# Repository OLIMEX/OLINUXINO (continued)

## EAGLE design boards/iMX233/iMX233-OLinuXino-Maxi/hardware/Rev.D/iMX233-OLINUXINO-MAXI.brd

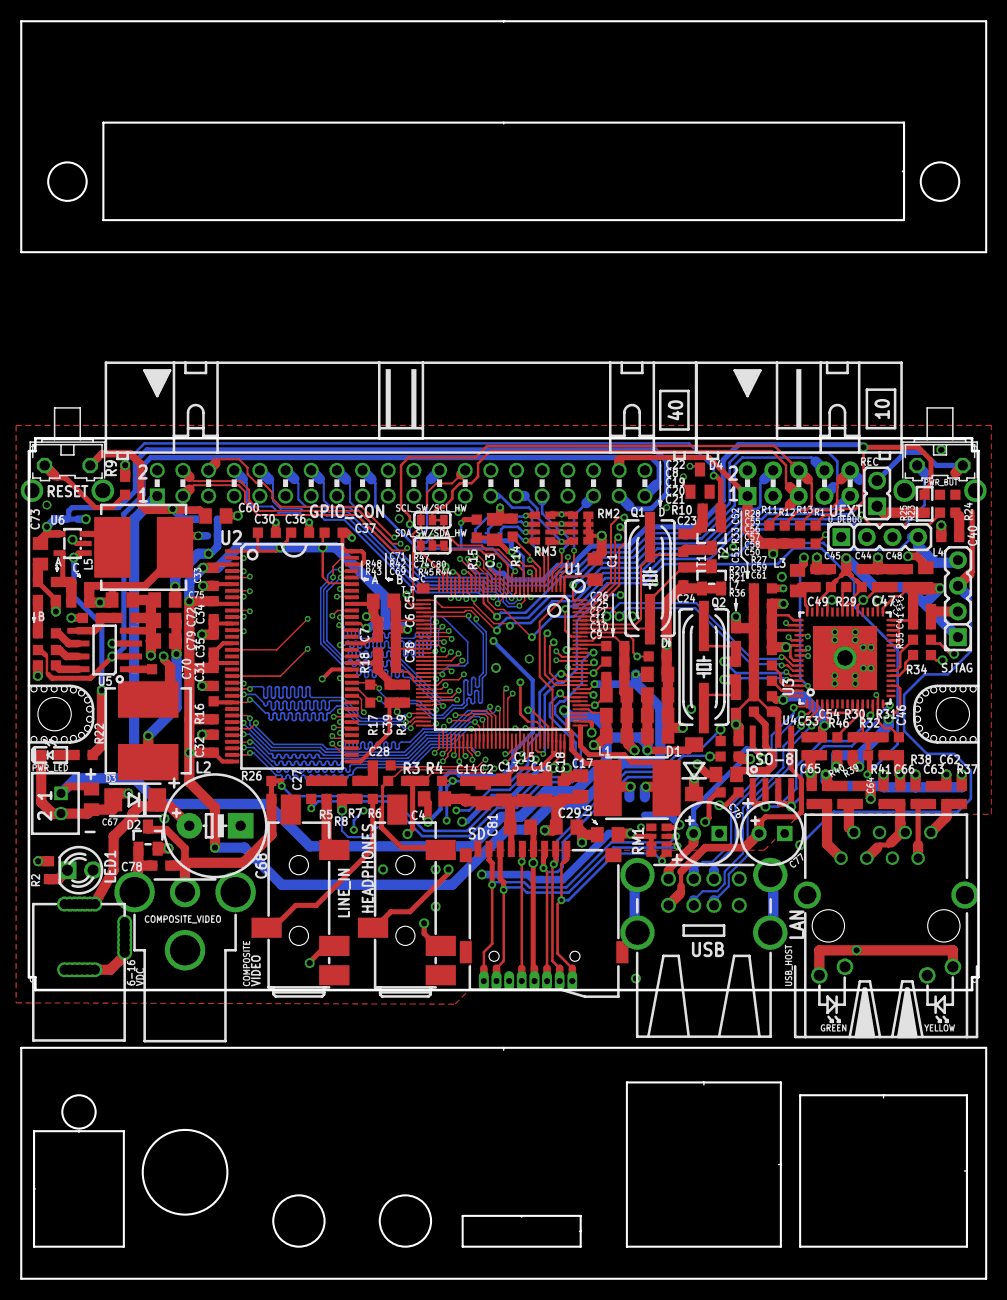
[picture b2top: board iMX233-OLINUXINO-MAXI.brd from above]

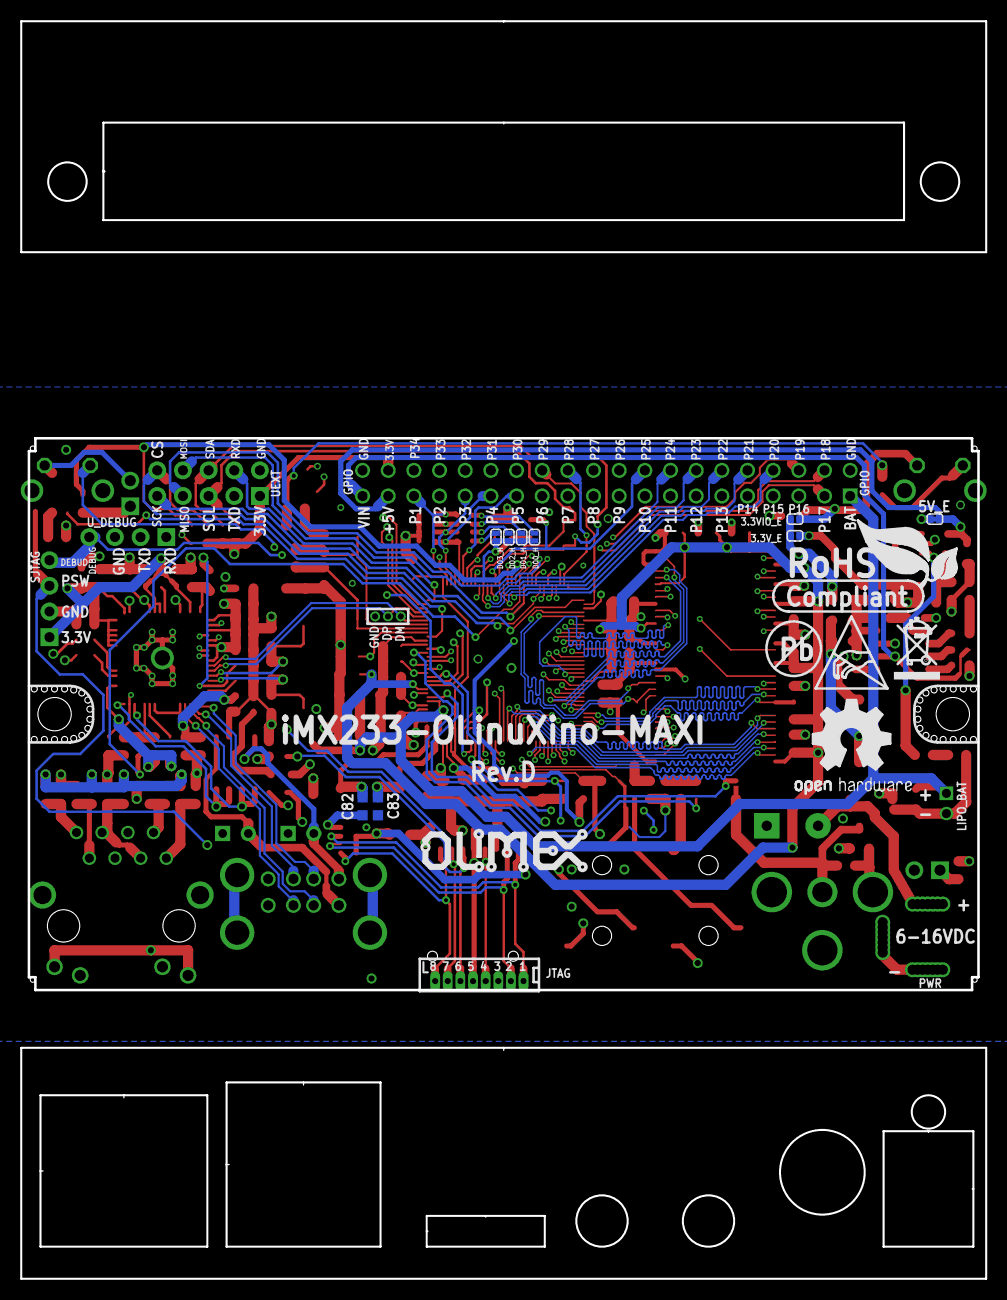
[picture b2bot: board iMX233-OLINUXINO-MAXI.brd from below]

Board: 4 copper layers, 94.0 x 54.6 mm, 191 parts (16 on the bottom side), 179 nets.

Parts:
3.3VIO_E: Open; SJ_1_SMALLER
3.3V_E: Close; SJ_1_SMALLER
5V_E: Close; SJ_1_SMALLER_CLOSE
C1, C2, C3, C4, C5, C8, C9, C10, C11, C13, C15, C16, C17, C19, C20, C21, C29, C60, C67, C72, C73, C75, C79, C80, C81: 22uF/6.3V; C0805_5MIL_DWS
C6, C7, C12, C14, C18, C22, C25, C30, C31, C32, C33, C34, C36, C38, C39, C40, C41, C42, C43, C44, C45, C46, C47, C49, C53, C54, C55, C56, C57, C58, C59, C69: 100nF; C0603_DWS
C23, C24: 10pF; C0603_DWS
C26, C27, C28: 1uF; C0603_DWS
C35, C37, C61: 10uF/10V; C0603_DWS
C48, C50: 4.7uF; C0603_DWS
C51, C52: 33pF; C0603_DWS
C62, C63, C64, C65: 15pF; C0603_DWS
C66: 22nF; C0603_DWS
C68: 470uF/25V/LOWESR/105C; E5-10,5
C70: 10nF; C0603_DWS
C71: 3.3nF; C0603_DWS
C74: 22pF; C0603_DWS
C76, C77: 100uF/16V/LOWESR/105C/6.3x11mm_RM2.5; E2,5-6,3
C78: 47pF; C0603_DWS
C82: NA; C0603_DWS
C83: 100pF; C0603_DWS
COMPOSITE_VIDEO: VIDEO_CON
D00_H, D03_H: Close; SJ_1_SMALLER
D1: SS14; MLL-41
D01_H, D02_H: Open; SJ_1_SMALLER
D2: BAT54S; SOT23C(BAT54S)
D3: SMBJ16A; DO214AA
D4: BAT54C; SOT23C
GND: TESTPADTESTPAD60/90_WITHOUT_MASK; TESTPAD60/90_WITHOUT_MASK
GPIO_CON: ML40R; BH40R
HEADPHONES: AUDIO_JACK_5PINPJ-W47S-05D2-LF_V2; PJ-W47S-05D2-LF_5PIN_V2
JTAG: NA(WU08S); WU08S
L1: 22uH/1.3A/SW68; CD53
L2: 10uH/2.3A/YS75/7x8; 8X8MM_3131
L3, L4, L7: FB0805/600R/2A; L0805_5MIL_DWS
L5: 2.2uH/3A/YS75/7x8; 8X8MM_3131
L6: CL470nH/0805/1.76R/250mA; L0805_5MIL_DWS
LAN: RJLD-043TC; RJLD-043TC_PACK
LED1: LED/GREEN/3MM; LED-3.0MM
LINE_IN: AUDIO_JACK_5PINPJ-W47S-05D2-LF_V2; PJ-W47S-05D2-LF_5PIN_V2
LIPO_BAT: DW02S
PWR: YDJ-1136; PWR_JACK_UNI_MILLING
PWR_BUT: TV-06B; B3F-31XX
PWR_LED: LED/RED/0603; LED-0603
Q1, Q2: HC49/S1; HC49/SMD2_THIN
R1, R7, R8: 4.7k; R0603_5MIL_DWS
R2, R34, R35, R36: 560R; R0603_5MIL_DWS
R3, R4, R17: 120R; R0603_5MIL_DWS
R5, R6, R16, R21, R29, R31, R46: 10k; R0603_5MIL_DWS
R9, R10, R13, R15, R42: 47k; R0603_5MIL_DWS
R11, R12, R43: 2.2k; R0603_5MIL_DWS
R14: NA(47k); R0603_5MIL_DWS
R18, R19: 1k/1%; R0603_5MIL_DWS
R20, R33: 1M; R0603_5MIL_DWS
R22, R23, R24: 1k; R0603_5MIL_DWS
R25: 10k; R0603_5MIL_DWS_NA
R26, R32: 0R(Board_Mounted); 0603_0R
R27: 12k/1%; R0603_5MIL_DWS
R28: 12.4k/1%; R0603_5MIL_DWS
R30: NA; R0603_5MIL_DWS
R37, R38, R39, R40: 49.9R/1%; R0603_5MIL_DWS
R41: 10R/1%; R0603_5MIL_DWS
R44, R48: 1.1k/1%; R0603_5MIL_DWS
R45, R47: 4.99k/1%; R0603_5MIL_DWS
REC: NA(HN1x2); JP1
RESET: TV-06B; B3F-31XX
RM1: RA1206_(4X0603)_4B8_100K; R_MATRIX_4
RM2: RA1206_(4X0603)_4B8_47K; R_MATRIX_4
RM3: RA1206_(4X0603)_4B8_4.7K; R_MATRIX_4
SCL_SW/SCL_HW: SCL_SW:Open/SCL_HW:Close; SJ_2_SMALL
SD: MICRO_SD/MMC_CP_NEWTFC-WPAPR-08; TFC-WPAPR-08
SDA_SW/SDA_HW: SDA_SW:Open/SDA_HW:Close; SJ_2_SMALL
SJTAG: (NA)HN1X4; HN1X4
T1, T2: BC846B; SOT23
T_P: TESTPAD50/40; SMD50/40
U1: MCIMX233CAG4C; TQFP128LD
U2: HY5DU121622D(L)T(P)-J; 66TSOP-II
U3: LAN9512-JZX; QFN64
U4: MIC2026-1YM; SO-8
U5: MP1482DS; SOIC8
U6: SY8008C(AA)C; SOT23-5
U$5: LOGO-OPENHARDWARE_8X8
U$6: JM42_PACTEC-101X61X25_MILLED
U$8: OLIMEX1_V
U$9: PB
U$10: ESD_SYMBOL
U$11: RECYCLE_BIN1/8
U$12: ROHS
UEXT: BH10R
USB_HOST: USB_TWO_LEVEL
U_DEBUG: HN1X4

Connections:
+5V: 5V_E.2, C11.2, C12.2, C73.1, GPIO_CON.37, L7.2, R22.1, U1.102, U6.1, U6.4
+15V: C68.+, D3.C, GPIO_CON.39, PWR.+, R42.1, U5.2
+24V: C19.2, C20.2, C21.2, C67.2, D1.A, GPIO_CON.1, LIPO_BAT.1, U1.100, U1.103
A0: U1.76, U2.29
A1: U1.75, U2.30
A2: U1.74, U2.31
A3: U1.73, U2.32
A4: U1.72, U2.35
A5: U1.71, U2.36
A6: U1.70, U2.37
A7: U1.69, U2.38
A8: U1.68, U2.39
A9: U1.67, U2.40
A10: U1.66, U2.28
A11: U1.65, U2.41
A12: U1.64, U2.42
AUART1_RXD: U1.128, UEXT.4
AUART1_TXD: U1.127, UEXT.3
BA0: U1.79, U2.26
BA1: U1.80, U2.27
CASN: U1.61, U2.22
CKE: U1.78, U2.44
CLK: R17.2, U1.36, U2.45
CLKN: R17.1, U1.37, U2.46
CS: R16.1, U1.63, U2.24
D0: U1.41, U2.2
D1: U1.43, U2.4
D2: U1.42, U2.5
D3: U1.44, U2.7
D4: U1.47, U2.8
D5: U1.48, U2.10
D6: U1.49, U2.11
D7: U1.50, U2.13
D8: U1.51, U2.54
D9: U1.52, U2.56
D10: U1.54, U2.57
D11: U1.55, U2.59
D12: U1.57, U2.60
D13: U1.58, U2.62
D14: U1.60, U2.63
D15: U1.59, U2.65
DCDC_VDDA: C17.2, C18.2, C25.2, U1.96, U1.110
DCDC_VDDD: C1.2, C2.2, C13.2, C14.2, U1.1, U1.93, U1.94
DEBUG: SJTAG.4, U1.89, U_DEBUG.4
DQM0: U1.46, U2.20
DQM1: U1.56, U2.47
DQS0: U1.39, U2.16
DQS1: U1.40, U2.51
GND: C1.1, C2.1, C3.1, C4.1, C5.1, C6.1, C7.1, C8.1, C9.1, C10.1, C11.1, C12.1, C13.1, C14.1, C15.1, C16.1, C17.1, C18.1, C19.1, C20.1, C21.1, C22.1, C23.1, C24.1, C25.1, C26.1, C29.1, C30.1, C31.1, C32.1, C33.1, C34.1, C35.1, C36.1, C37.1, C39.1, C40.2, C41.1, C42.1, C43.1, C44.1, C45.1, C46.1, C47.1, C48.1, C49.1, C50.1, C51.2, C52.2, C53.2, C54.2, C55.2, C56.2, C57.2, C58.2, C59.2, C60.2, C61.2, C62.2, C63.2, C64.2, C65.2, C66.2, C67.1, C68.-, C69.2, C72.2, C73.2, C75.2, C76.-, C77.-, C78.2, C79.2, C80.2, C81.1, C82.1, C83.1, COMPOSITE_VIDEO.GND1, COMPOSITE_VIDEO.GND2, COMPOSITE_VIDEO.GND3, D2.1, GND.P$1, GPIO_CON.2, GPIO_CON.40, JTAG.3, LINE_IN.5, LIPO_BAT.2, PWR.-, PWR.--, PWR_LED.C, R2.1, R7.1, R8.1, R10.2, R14.1, R19.1, R20.2, R27.1, R28.1, R31.1, R36.1, R43.2, R44.2, R48.2, RM1.4.1, RM2.1.1, RM2.2.1, RM2.3.1, RM2.4.1, SD.6, SJTAG.2, T1.1, T1.2, T2.2, U1.30, U1.35, U1.98, U1.105, U1.112, U1.118, U2.6, U2.12, U2.34, U2.48, U2.52, U2.58, U2.64, U2.66, U3.34, U3.44, U3.65, U4.6, U5.4, U6.2, UEXT.2, USB_HOST.1.4, USB_HOST.2.4, U_DEBUG.3
HP_VGND: HEADPHONES.5, R3.1, R4.1, U1.111
I2C_SCL: R11.1, SCL_SW/SCL_HW.2, UEXT.5
I2C_SDA: R12.1, SDA_SW/SDA_HW.2, UEXT.6
LED1: LED1.A, U1.88
unnamed: C61.1, L7.1, U4.7
unnamed: C46.2, C47.2, C48.2, U3.15, U3.38
unnamed: C49.2, L3.2, U3.48
unnamed: C78.1, COMPOSITE_VIDEO.IO, D2.3, R26.2
unnamed: R46.2, U3.11
unnamed: LINE_IN.2, R5.2
unnamed: C38.2, C39.2, R18.1, R19.2, U2.49
unnamed: R25.1, REC.1
unnamed: R24.2, RM1.4.2
unnamed: D4.3, U_DEBUG.1
unnamed: C50.2, L3.1, U3.62
unnamed: R27.2, U3.63
unnamed: HEADPHONES.2, R3.2, U1.113
unnamed: R28.2, U3.50
unnamed: C82.2, L1.2, U1.97
unnamed: C83.2, L1.1, U1.99
unnamed: HEADPHONES.3, R4.2, U1.109
unnamed: 5V_E.1, C72.1, C79.1, L2.2, R45.2
unnamed: R29.2, U3.41
unnamed: C26.2, U1.117
unnamed: LINE_IN.3, R6.2
unnamed: C51.1, Q2.2, R33.2, U3.61
unnamed: C28.1, R6.1, R7.2
unnamed: C27.1, R5.1, R8.2
unnamed: C27.2, U1.115
unnamed: C28.2, U1.114
unnamed: C69.1, U5.8
unnamed: R42.2, U5.7
unnamed: C40.1, R24.1
unnamed: C52.1, Q2.1, R33.1, U3.60
unnamed: R34.1, U3.21
unnamed: R35.1, U3.22
unnamed: LED1.K, R2.2
unnamed: R9.1, R10.1, T2.1
unnamed: LAN.KG, R34.2
unnamed: C70.1, U5.1
unnamed: LAN.KY, R35.2
unnamed: C62.1, LAN.8, R37.1, U3.53
unnamed: R30.2, R31.2, R32.2, U3.12
unnamed: C70.2, L2.1, U5.3
unnamed: C63.1, LAN.7, R38.1, U3.52
unnamed: C64.1, LAN.2, R39.1, U3.56
unnamed: C65.1, LAN.1, R40.1, U3.55
unnamed: C66.1, LAN.3, LAN.6, R41.1
unnamed: U3.1, USB_HOST.1.2
unnamed: U3.2, USB_HOST.1.3
unnamed: U3.3, USB_HOST.2.2
unnamed: U3.4, USB_HOST.2.3
unnamed: R36.2, USB_HOST.GND1, USB_HOST.GND2, USB_HOST.GND3, USB_HOST.GND4
unnamed: C71.1, U5.6
unnamed: C71.2, R43.1
unnamed: R44.1, R45.1, U5.5
unnamed: L5.1, U6.3
unnamed: 3.3V_E.1, C74.1, C80.1, L5.2, R47.1
unnamed: C74.2, R47.2, R48.1, U6.5
unnamed: D03_H.1, RM3.1.2
unnamed: D02_H.1, RM3.2.2
unnamed: D01_H.1, RM3.3.2
unnamed: D00_H.1, RM3.4.2
unnamed: PWR_LED.A, R22.2
PIN1/LCD_D00: GPIO_CON.35, RM2.4.2, RM3.4.1, U1.2
PIN2/LCD_D01: GPIO_CON.33, RM2.3.2, RM3.3.1, U1.3
PIN3/LCD_D02: GPIO_CON.31, RM2.2.2, RM3.2.1, U1.4
PIN4/LCD_D03: GPIO_CON.29, RM2.1.2, RM3.1.1, U1.5
PIN5/LCD_D04: GPIO_CON.27, U1.6
PIN6/LCD_D05: GPIO_CON.25, R14.2, U1.7
PIN7/LCD_D06: GPIO_CON.23, U1.8
PIN8/LCD_D07: GPIO_CON.21, U1.9
PIN9/LCD_D08/SSP2_MISO: GPIO_CON.19, U1.22, UEXT.7
PIN10/LCD_D09: GPIO_CON.17, U1.23
PIN11/LCD_D10: GPIO_CON.15, U1.24
PIN12/LCD_D11/UEXT_CS: GPIO_CON.13, R13.1, U1.25, UEXT.10
PIN13/LCD_D12: GPIO_CON.11, U1.27
PIN14/LCD_D13: GPIO_CON.9, U1.26
PIN15/LCD_D14: GPIO_CON.7, U1.29
PIN16/LCD_D15: GPIO_CON.5, U1.28
PIN17/LCD_D16: GPIO_CON.3, U1.19
PIN18/LCD_D17/LAN_RES: GPIO_CON.4, R32.1, U1.20
PIN19/LCD_DOTCLK: GPIO_CON.6, U1.17
PIN20/LCD_VSYNC: GPIO_CON.8, U1.16
PIN21/LCD_HSYNC/I2C_SDA: GPIO_CON.10, SDA_SW/SDA_HW.1, U1.15
PIN22/LCD_EN/I2C_SCL: GPIO_CON.12, SCL_SW/SCL_HW.1, U1.11
PIN23/LCD_DISP: GPIO_CON.14, U1.12
PIN24/LCD_WR: GPIO_CON.16, U1.13
PIN25/LCD_RS: GPIO_CON.18, R15.2, U1.14
PIN26/LCD_CS: GPIO_CON.20, U1.10
PIN27/PWM2: GPIO_CON.22, U1.91
PIN28/SOFT_SDA: GPIO_CON.24, SDA_SW/SDA_HW.3, U1.31
PIN29/SOFT_SCL: GPIO_CON.26, SCL_SW/SCL_HW.3, U1.34
PIN30: GPIO_CON.28, U1.81
PIN31: GPIO_CON.30, U1.82
PIN32/LRADC1: GPIO_CON.32, U1.107
PIN33/LRADC0: GPIO_CON.34, U1.108
PIN34/MIC: GPIO_CON.36, U1.116
PRTCTL2: U3.14, U4.1, U4.2
PRTCTL3: U3.16, U4.3, U4.4
PSWITCH: R23.1, U1.119
PWM0/DUART_RXD: D4.1, R1.1, U1.125
PWM1/DUART_TXD: U1.126, U_DEBUG.2
RASN: U1.62, U2.23
RESET: R9.2, RESET.2
SD_VCC: C29.2, C81.2, JTAG.5, L6.2, SD.4
SJTAG_PSW: PWR_BUT.1, R23.2, REC.2, SJTAG.3
SSP1_CMD: JTAG.6, R21.1, SD.3, U1.83
SSP1_DATA0: JTAG.2, RM1.2.1, SD.7, U1.84
SSP1_DATA1: JTAG.1, RM1.3.1, SD.8, U1.85
SSP1_DATA2: JTAG.8, RM1.1.1, SD.1, U1.86
SSP1_DATA3: JTAG.7, R20.1, SD.2, U1.87
SSP1_SCK: JTAG.4, SD.5, U1.90
SSP2_MOSI: U1.21, UEXT.8
SSP2_SCK: U1.33, UEXT.9
TEST_PAD: T_P.P$1, U1.32
USB_DM: U1.123, U3.58
USB_DP: U1.124, U3.59
USB_PWR_A: C76.+, U4.8, USB_HOST.1.1
USB_PWR_B: C77.+, U4.5, USB_HOST.2.1
V+: C5.2, C6.2, C7.2, C8.2, C30.2, C31.2, C32.2, C33.2, C34.2, C35.2, C36.2, C37.2, C38.1, R16.2, R18.2, U1.38, U1.45, U1.53, U1.106, U2.1, U2.3, U2.9, U2.15, U2.18, U2.33, U2.55, U2.61
VCC: 3.3VIO_E.1, 3.3V_E.2, C41.2, C42.2, C43.2, C44.2, C45.2, C75.1, GPIO_CON.38, L4.1, LAN.AG, LAN.AY, R11.2, R12.2, R13.2, R29.1, R30.1, R46.1, SJTAG.1, U3.19, U3.27, U3.28, U3.29, U3.30, U3.32, U3.33, U3.39, U3.40, U3.46, UEXT.1
VDAC1: R26.1, U1.104
VDD: C53.1, C54.1, C55.1, C56.1, C57.1, C58.1, C59.1, L4.2, R37.2, R38.2, R39.2, R40.2, R41.2, U3.5, U3.10, U3.49, U3.51, U3.54, U3.57, U3.64
VDD4P2: C9.2, C10.2, D1.K, U1.101
VDDXTAL: C22.2, PWR_BUT.2, U1.120
VPP: 3.3VIO_E.2, C3.2, C4.2, C15.2, C16.2, C60.1, D00_H.2, D01_H.2, D2.2, D02_H.2, D03_H.2, L6.1, R1.2, R15.1, R21.2, R25.2, RESET.1, RM1.1.2, RM1.2.2, RM1.3.2, U1.18, U1.92, U1.95
WEN: U1.77, U2.21
XTALI: C23.2, Q1.2, T2.3, U1.122
XTALO: C24.2, Q1.1, T1.3, U1.121

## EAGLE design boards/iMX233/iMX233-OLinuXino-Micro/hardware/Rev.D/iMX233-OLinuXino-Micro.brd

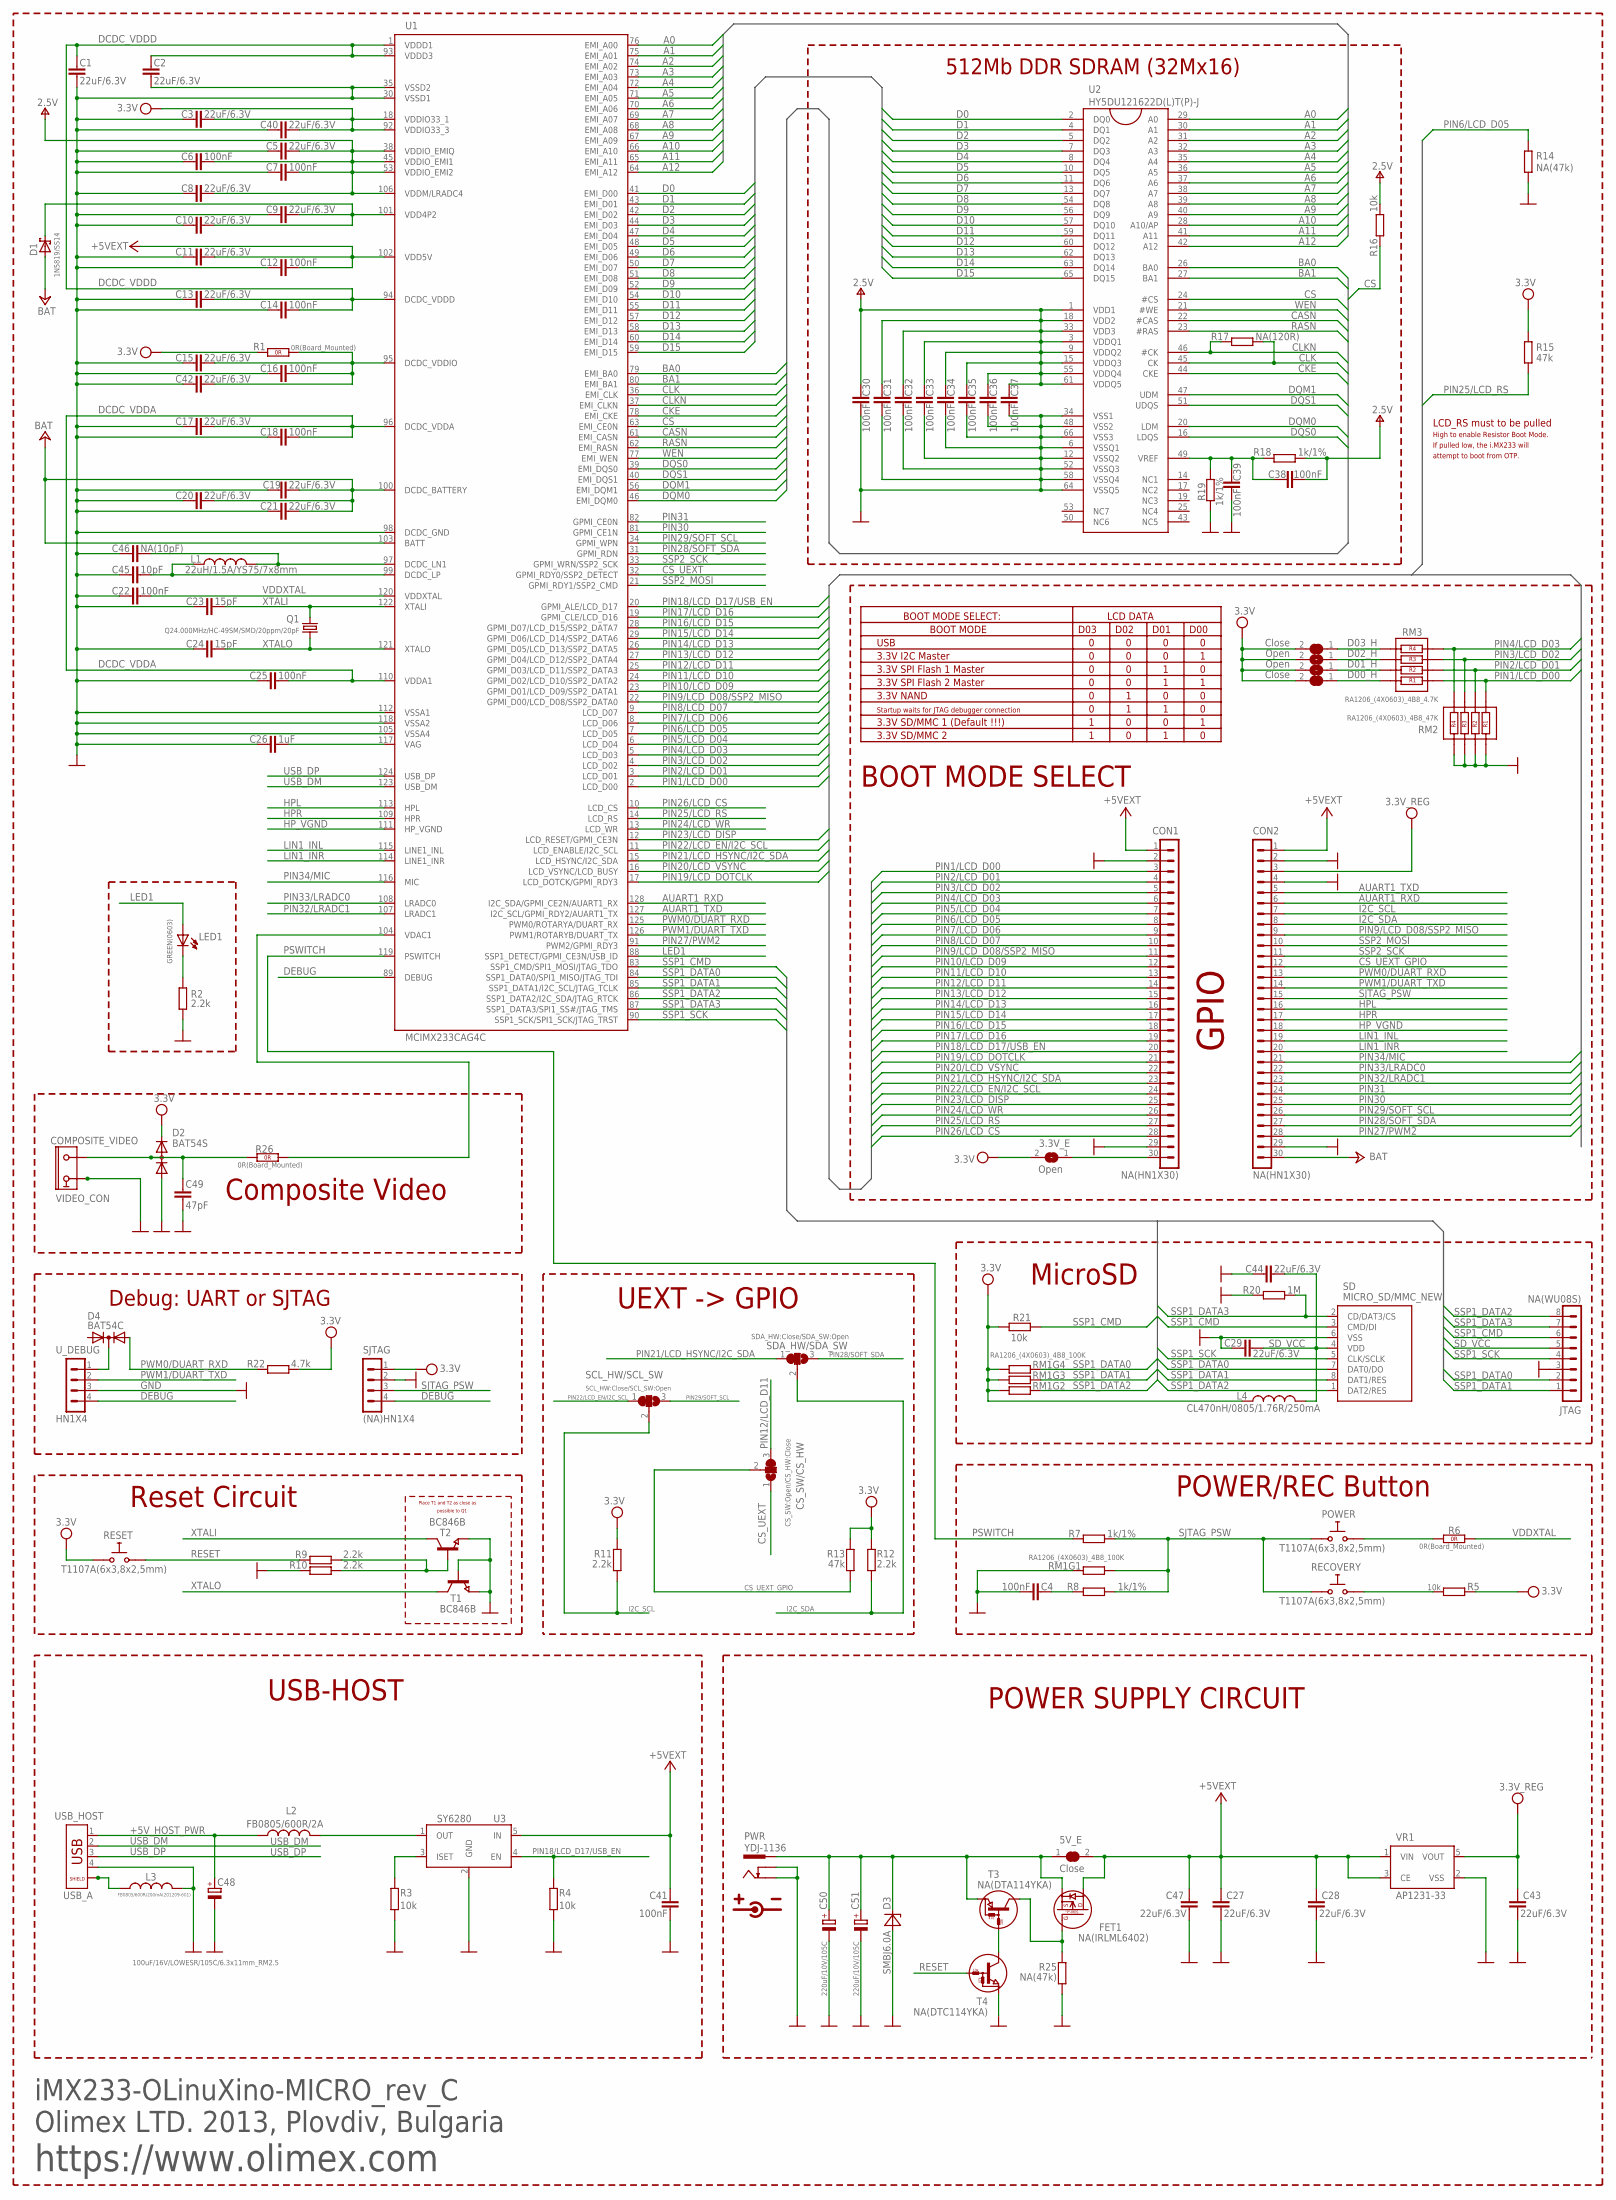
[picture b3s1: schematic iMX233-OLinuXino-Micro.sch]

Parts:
3.3V_E: Open; SJ_1_SMALLER
5V_E: Close; SJ-CLOSE
C1, C2, C5, C8, C9, C10, C11, C13, C15, C17, C19, C20, C21, C27, C28, C29, C40, C42, C43, C44, C47: 22uF/6.3V; C0603_DWS
C3: 22uF/6.3V; C1206
C4, C6, C7, C12, C14, C16, C18, C22, C25, C30, C31, C32, C33, C34, C35, C36, C37, C38, C39, C41: 100nF; C0603_DWS
C23, C24: 15pF; C0603_DWS
C26: 1uF; C0603_DWS
C45: 10pF; C0603_DWS
C46: NA(10pF); C0603_DWS
C48: 100uF/16V/LOWESR/105C/6.3x11mm_RM2.5; E2,5-6,3
C49: 47pF; C0603_DWS
C50, C51: 220uF/10V/105C; E2,5-6,3
COMPOSITE_VIDEO: VIDEO_CON; VIDEO_CINCH
CON1, CON2: NA(HN1X30); HN1X30
CS_SW/CS_HW: CS_SW:Open/CS_HW:Close; SJ_2_SMALL
D00_H, D03_H: Close; SJ_1_SMALLER
D1: 1N5819/SS14; MLL-41
D01_H, D02_H: Open; SJ_1_SMALLER
D2: BAT54S; SOT23C(BAT54S)
D3: SMBJ6.0A; DO214AA
D4: BAT54C; SOT23C
FET1: NA(IRLML6402); SOT23
JTAG: NA(WU08S); WU08S
L1: 22uH/1.5A/YS75/7x8mm; L7078
L2: FB0805/600R/2A; L0805_5MIL_DWS
L3: FB0805/600R/200mA(201209-601); L0805_5MIL_DWS
L4: CL470nH/0805/1.76R/250mA; L0805_5MIL_DWS
LED1: GREEN(0603); LED-0603
POWER: T1107A(6x3,8x2,5mm); SW-TAKT_6X3.5_SMD
PWR: YDJ-1136; PWR_JACK_UNI_MILLING
Q1: Q24.000MHz/HC-49SM/SMD/20ppm/20pF; HC49/SMD2_THIN
R1, R6, R26: 0R(Board_Mounted); 0603_0R
R2, R9, R10, R11, R12: 2.2k; R0603_5MIL_DWS
R3, R4, R5, R16, R21: 10k; R0603_5MIL_DWS
R7, R8, R18, R19: 1k/1%; R0603_5MIL_DWS
R13, R15: 47k; R0603_5MIL_DWS
R14, R25: NA(47k); R0603_5MIL_DWS
R17: NA(120R); R0603_5MIL_DWS
R20: 1M; R0603_5MIL_DWS
R22: 4.7k; R0603_5MIL_DWS
RECOVERY: T1107A(6x3,8x2,5mm); SW-TAKT_6X3.5_SMD
RESET: T1107A(6x3,8x2,5mm); SW-TAKT_6X3.5_SMD
RM1: RA1206_(4X0603)_4B8_100K; R_MATRIX_4
RM2: RA1206_(4X0603)_4B8_47K; R_MATRIX_4
RM3: RA1206_(4X0603)_4B8_4.7K; R_MATRIX_4
SCL_HW/SCL_SW: SCL_HW:Close/SCL_SW:Open; SJ_2_SMALL
SD: MICRO_SD/MMC_NEW; TFR/C-MEM-CON
SDA_HW/SDA_SW: SDA_HW:Close/SDA_SW:Open; SJ_2_SMALL
SJTAG: (NA)HN1X4; HN1X4
T1, T2: BC846B; SOT23
T3: NA(DTA114YKA); SOT-23
T4: NA(DTC114YKA); SOT-23
U1: MCIMX233CAG4C; TQFP128LD
U2: HY5DU121622D(L)T(P)-J; 66TSOP-II
U3: SY6280; SOT23-5
USB_HOST: USB_A; USB_PN87520_HOST_PTH
U_DEBUG: HN1X4
VR1: AP1231-33; SOT-23-5

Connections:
+5V: 5V_E.2, C11.2, C12.2, C27.1, C28.1, C41.1, C47.1, CON1.1, CON2.1, FET1.3 (D), U1.102 (VDD5V), U3.5 (IN), VR1.1 (VIN), VR1.3 (CE)
+5V_HOST_PWR: C48.+, L2.1, USB_HOST.1
+24V: C19.2, C20.2, C21.2, CON2.30, D1.A, U1.100 (DCDC_BATTERY), U1.103 (BATT)
A0: U1.76 (EMI_A00), U2.29 (A0)
A1: U1.75 (EMI_A01), U2.30 (A1)
A2: U1.74 (EMI_A02), U2.31 (A2)
A3: U1.73 (EMI_A03), U2.32 (A3)
A4: U1.72 (EMI_A04), U2.35 (A4)
A5: U1.71 (EMI_A05), U2.36 (A5)
A6: U1.70 (EMI_A06), U2.37 (A6)
A7: U1.69 (EMI_A07), U2.38 (A7)
A8: U1.68 (EMI_A08), U2.39 (A8)
A9: U1.67 (EMI_A09), U2.40 (A9)
A10: U1.66 (EMI_A10), U2.28 (A10/AP)
A11: U1.65 (EMI_A11), U2.41 (A11)
A12: U1.64 (EMI_A12), U2.42 (A12)
AUART1_RXD: CON2.6, U1.128 (I2C_SDA/GPMI_CE2N/AUART1_RX)
AUART1_TXD: CON2.5, U1.127 (I2C_SCL/GPMI_RDY2/AUART1_TX)
BA0: U1.79 (EMI_BA0), U2.26 (BA0)
BA1: U1.80 (EMI_BA1), U2.27 (BA1)
CASN: U1.61 (EMI_CASN), U2.22 (#CAS)
CKE: U1.78 (EMI_CKE), U2.44 (CKE)
CLK: R17.2, U1.36 (EMI_CLK), U2.45 (CK)
CLKN: R17.1, U1.37 (EMI_CLKN), U2.46 (#CK)
CS: R16.1, U1.63 (EMI_CE0N), U2.24 (#CS)
CS_UEXT: CS_SW/CS_HW.1, U1.32 (GPMI_RDY0/SSP2_DETECT)
CS_UEXT_GPIO: CON2.12, CS_SW/CS_HW.2, R13.1
D0: U1.41 (EMI_D00), U2.2 (DQ0)
D1: U1.43 (EMI_D01), U2.4 (DQ1)
D2: U1.42 (EMI_D02), U2.5 (DQ2)
D3: U1.44 (EMI_D03), U2.7 (DQ3)
D4: U1.47 (EMI_D04), U2.8 (DQ4)
D5: U1.48 (EMI_D05), U2.10 (DQ5)
D6: U1.49 (EMI_D06), U2.11 (DQ6)
D7: U1.50 (EMI_D07), U2.13 (DQ7)
D8: U1.51 (EMI_D08), U2.54 (DQ8)
D9: U1.52 (EMI_D09), U2.56 (DQ9)
D10: U1.54 (EMI_D10), U2.57 (DQ10)
D11: U1.55 (EMI_D11), U2.59 (DQ11)
D12: U1.57 (EMI_D12), U2.60 (DQ12)
D13: U1.58 (EMI_D13), U2.62 (DQ13)
D14: U1.60 (EMI_D14), U2.63 (DQ14)
D15: U1.59 (EMI_D15), U2.65 (DQ15)
DCDC_VDDA: C17.2, C18.2, C25.2, U1.96 (DCDC_VDDA), U1.110 (VDDA1)
DCDC_VDDD: C1.2, C2.2, C13.2, C14.2, U1.1 (VDDD1), U1.93 (VDDD3), U1.94 (DCDC_VDDD)
DCDC_VDDIO: C15.2, C16.2, C42.2, R1.2 (1.2), U1.95 (DCDC_VDDIO)
DEBUG: SJTAG.4, U1.89 (DEBUG), U_DEBUG.4
DQM0: U1.46 (EMI_DQM0), U2.20 (LDM)
DQM1: U1.56 (EMI_DQM1), U2.47 (UDM)
DQS0: U1.39 (EMI_DQS0), U2.16 (LDQS)
DQS1: U1.40 (EMI_DQS1), U2.51 (UDQS)
GND: C1.1, C2.1, C3.1, C4.2, C5.1, C6.1, C7.1, C8.1, C9.1, C10.1, C11.1, C12.1, C13.1, C14.1, C15.1, C16.1, C17.1, C18.1, C19.1, C20.1, C21.1, C22.1, C23.1, C24.1, C25.1, C26.1, C27.2, C28.2, C29.1, C30.1, C31.1, C32.1, C33.1, C34.1, C35.1, C36.1, C37.1, C39.1, C40.1, C41.2, C42.1, C43.2, C44.1, C45.1, C46.1, C47.2, C48.-, C49.2, C50.-, C51.-, COMPOSITE_VIDEO.GND1 (GND), COMPOSITE_VIDEO.GND1A (GND), COMPOSITE_VIDEO.GND1B (GND), COMPOSITE_VIDEO.GND1C (GND), COMPOSITE_VIDEO.GND1D (GND), COMPOSITE_VIDEO.GND1E (GND), COMPOSITE_VIDEO.GND2 (GND), COMPOSITE_VIDEO.GND3 (GND), COMPOSITE_VIDEO.GND3C (GND), COMPOSITE_VIDEO.GND3D (GND), COMPOSITE_VIDEO.GND3E (GND), COMPOSITE_VIDEO.GNG3A (GND), COMPOSITE_VIDEO.GNG3B (GND), CON1.2, CON1.29, CON2.2, CON2.4, CON2.29, D2.1 (A), D3.A, JTAG.3, L3.1, PWR.-, PWR.--, R2.1, R3.1, R4.1, R10.2, R14.1, R19.1, R20.2, R25.1, RM1.1.1 (1), RM2.1.2, RM2.2.2, RM2.3.2, RM2.4.2, SD.6 (VSS), SJTAG.2, T1.1 (B), T1.2 (E), T2.2 (E), T4.2 (E), U1.30 (VSSD1), U1.35 (VSSD2), U1.98 (DCDC_GND), U1.105 (VSSA4), U1.112 (VSSA1), U1.118 (VSSA2), U2.6 (VSSQ1), U2.12 (VSSQ2), U2.34 (VSS1), U2.48 (VSS2), U2.52 (VSSQ3), U2.58 (VSSQ4), U2.64 (VSSQ5), U2.66 (VSS3), U3.2 (GND), USB_HOST.4, U_DEBUG.3, VR1.2 (VSS); also elsewhere on the board
HPL: CON2.16, U1.113 (HPL)
HPR: CON2.17, U1.109 (HPR)
HP_VGND: CON2.18, U1.111 (HP_VGND)
I2C_SCL: CON2.7, R11.1, SCL_HW/SCL_SW.2
I2C_SDA: CON2.8, R12.1, SDA_HW/SDA_SW.2
LED1: LED1.A, U1.88 (SSP1_DETECT/GPMI_CE3N/USB_ID)
LIN1_INL: CON2.19, U1.115 (LINE1_INL)
LIN1_INR: CON2.20, U1.114 (LINE1_INR)
unnamed: POWER.P$1 (0), R6.1 (1.1)
unnamed: 3.3V_E.1, CON1.30
unnamed: 5V_E.1, C50.+, C51.+, D3.C, FET1.2 (S), PWR.+, T3.2 (E)
unnamed: C49.1, COMPOSITE_VIDEO.IO, D2.3 (AK), R26.2 (1.2)
unnamed: L2.2, U3.1 (OUT)
unnamed: R3.2, U3.3 (ISET)
unnamed: C38.2, C39.2, R18.1, R19.2, U2.49 (VREF)
unnamed: R5.1, RECOVERY.P$1 (0)
unnamed: D4.3 (K), U_DEBUG.1
unnamed: FET1.1 (G), R25.2, T3.3 (C)
unnamed: T3.1 (B), T4.3 (C)
unnamed: C46.2, L1.2, U1.97 (DCDC_LN1)
unnamed: C45.2, L1.1, U1.99 (DCDC_LP)
unnamed: C26.2, U1.117 (VAG)
unnamed: C4.1, R8.1
unnamed: LED1.C, R2.2
unnamed: R9.1, R10.1, T2.1 (B)
unnamed: D03_H.1, RM3.4.1
unnamed: D02_H.1, RM3.3.1
unnamed: D01_H.1, RM3.2.1
unnamed: D00_H.1, RM3.1.1
unnamed: L3.2, USB_HOST.P$1 (5), USB_HOST.P$2 (6)
PIN1/LCD_D00: CON1.3, RM2.1.1, RM3.1.2, U1.2 (LCD_D00)
PIN2/LCD_D01: CON1.4, RM2.2.1, RM3.2.2, U1.3 (LCD_D01)
PIN3/LCD_D02: CON1.5, RM2.3.1, RM3.3.2, U1.4 (LCD_D02)
PIN4/LCD_D03: CON1.6, RM2.4.1, RM3.4.2, U1.5 (LCD_D03)
PIN5/LCD_D04: CON1.7, U1.6 (LCD_D04)
PIN6/LCD_D05: CON1.8, R14.2, U1.7 (LCD_D05)
PIN7/LCD_D06: CON1.9, U1.8 (LCD_D06)
PIN8/LCD_D07: CON1.10, U1.9 (LCD_D07)
PIN9/LCD_D08/SSP2_MISO: CON1.11, CON2.9, U1.22 (GPMI_D00/LCD_D08/SSP2_DATA0)
PIN10/LCD_D09: CON1.12, U1.23 (GPMI_D01/LCD_D09/SSP2_DATA1)
PIN11/LCD_D10: CON1.13, U1.24 (GPMI_D02/LCD_D10/SSP2_DATA2)
PIN12/LCD_D11: CON1.14, CS_SW/CS_HW.3, U1.25 (GPMI_D03/LCD_D11/SSP2_DATA3)
PIN13/LCD_D12: CON1.15, U1.27 (GPMI_D04/LCD_D12/SSP2_DATA4)
PIN14/LCD_D13: CON1.16, U1.26 (GPMI_D05/LCD_D13/SSP2_DATA5)
PIN15/LCD_D14: CON1.17, U1.29 (GPMI_D06/LCD_D14/SSP2_DATA6)
PIN16/LCD_D15: CON1.18, U1.28 (GPMI_D07/LCD_D15/SSP2_DATA7)
PIN17/LCD_D16: CON1.19, U1.19 (GPMI_CLE/LCD_D16)
PIN18/LCD_D17/USB_EN: CON1.20, R4.2, U1.20 (GPMI_ALE/LCD_D17), U3.4 (EN)
PIN19/LCD_DOTCLK: CON1.21, U1.17 (LCD_DOTCK/GPMI_RDY3)
PIN20/LCD_VSYNC: CON1.22, U1.16 (LCD_VSYNC/LCD_BUSY)
PIN21/LCD_HSYNC/I2C_SDA: CON1.23, SDA_HW/SDA_SW.1, U1.15 (LCD_HSYNC/I2C_SDA)
PIN22/LCD_EN/I2C_SCL: CON1.24, SCL_HW/SCL_SW.1, U1.11 (LCD_ENABLE/I2C_SCL)
PIN23/LCD_DISP: CON1.25, U1.12 (LCD_RESET/GPMI_CE3N)
PIN24/LCD_WR: CON1.26, U1.13 (LCD_WR)
PIN25/LCD_RS: CON1.27, R15.2, U1.14 (LCD_RS)
PIN26/LCD_CS: CON1.28, U1.10 (LCD_CS)
PIN27/PWM2: CON2.28, U1.91 (PWM2/GPMI_RDY3)
PIN28/SOFT_SDA: CON2.27, SDA_HW/SDA_SW.3, U1.31 (GPMI_RDN)
PIN29/SOFT_SCL: CON2.26, SCL_HW/SCL_SW.3, U1.34 (GPMI_WPN)
PIN30: CON2.25, U1.81 (GPMI_CE1N)
PIN31: CON2.24, U1.82 (GPMI_CE0N)
PIN32/LRADC1: CON2.23, U1.107 (LRADC1)
PIN33/LRADC0: CON2.22, U1.108 (LRADC0)
PIN34/MIC: CON2.21, U1.116 (MIC)
PSWITCH: R7.1, U1.119 (PSWITCH)
PWM0/DUART_RXD: CON2.13, D4.2 (A2), R22.2, U1.125 (PWM0/ROTARYA/DUART_RX)
PWM1/DUART_TXD: CON2.14, U1.126 (PWM1/ROTARYB/DUART_TX), U_DEBUG.2
RASN: U1.62 (EMI_RASN), U2.23 (#RAS)
RESET: R9.2, RESET.P$1 (0), T4.1 (B)
SD_VCC: C29.2, C44.2, JTAG.5, L4.2, SD.4 (VDD); also elsewhere on the board
SJTAG_PSW: CON2.15, POWER.P$2 (1), R7.2, R8.2, RECOVERY.P$2 (1), RM1.1.2 (2), SJTAG.3
SSP1_CMD: JTAG.6, R21.1, SD.3 (CMD/DI), U1.83 (SSP1_CMD/SPI1_MOSI/JTAG_TDO); also elsewhere on the board
SSP1_DATA0: JTAG.2, RM1.4.1 (1), SD.7 (DAT0/DO), U1.84 (SSP1_DATA0/SPI1_MISO/JTAG_TDI); also elsewhere on the board
SSP1_DATA1: JTAG.1, RM1.3.1 (1), SD.8 (DAT1/RES), U1.85 (SSP1_DATA1/I2C_SCL/JTAG_TCLK); also elsewhere on the board
SSP1_DATA2: JTAG.8, RM1.2.1 (1), SD.1 (DAT2/RES), U1.86 (SSP1_DATA2/I2C_SDA/JTAG_RTCK); also elsewhere on the board
SSP1_DATA3: JTAG.7, R20.1, SD.2 (CD/DAT3/CS), U1.87 (SSP1_DATA3/SPI1_SS#/JTAG_TMS); also elsewhere on the board
SSP1_SCK: JTAG.4, SD.5 (CLK/SCLK), U1.90 (SSP1_SCK/SPI1_SCK/JTAG_TRST); also elsewhere on the board
SSP2_MOSI: CON2.10, U1.21 (GPMI_RDY1/SSP2_CMD)
SSP2_SCK: CON2.11, U1.33 (GPMI_WRN/SSP2_SCK)
USB_DM: U1.123 (USB_DM), USB_HOST.2
USB_DP: U1.124 (USB_DP), USB_HOST.3
V+: C5.2, C6.2, C7.2, C8.2, C30.2, C31.2, C32.2, C33.2, C34.2, C35.2, C36.2, C37.2, C38.1, R16.2, R18.2, U1.38 (VDDIO_EMIQ), U1.45 (VDDIO_EMI1), U1.53 (VDDIO_EMI2), U1.106 (VDDM/LRADC4), U2.1 (VDD1), U2.3 (VDDQ1), U2.9 (VDDQ2), U2.15 (VDDQ3), U2.18 (VDD2), U2.33 (VDD3), U2.55 (VDDQ4), U2.61 (VDDQ5)
VCC: 3.3V_E.2, C3.2, C40.2, D00_H.2, D01_H.2, D2.2 (K), D02_H.2, D03_H.2, L4.1, R1.1 (1.1), R5.2, R11.2, R12.2, R13.2, R15.1, R21.2, R22.1, RESET.P$2 (1), RM1.2.2 (2), RM1.3.2 (2), RM1.4.2 (2), SJTAG.1, U1.18 (VDDIO33_1), U1.92 (VDDIO33_3)
VDAC1: R26.1 (1.1), U1.104 (VDAC1)
VDD4P2: C9.2, C10.2, D1.K (C), U1.101 (VDD4P2)
VDDXTAL: C22.2, R6.2 (1.2), U1.120 (VDDXTAL)
VPP: C43.1, CON2.3, VR1.5 (VOUT)
WEN: U1.77 (EMI_WEN), U2.21 (#WE)
XTALI: C23.2, Q1.2, T2.3 (C), U1.122 (XTALI)
XTALO: C24.2, Q1.1, T1.3 (C), U1.121 (XTALO)

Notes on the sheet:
POWER SUPPLY CIRCUIT
Place T1 and T2 as close as
possible to Q1
Reset Circuit
512Mb DDR SDRAM (32Mx16)
MicroSD
Composite Video
POWER/REC Button
BOOT MODE SELECT
UEXT -> GPIO
BOOT MODE SELECT:
LCD DATA
BOOT MODE
D03
D02
D01
D00
USB
3.3V I2C Master
3.3V SPI Flash 1 Master
3.3V SPI Flash 2 Master
3.3V NAND
Startup waits for JTAG debugger connection
3.3V SD/MMC 1 (Default !!!)
3.3V SD/MMC 2
LCD_RS must to be pulled
High to enable Resistor Boot Mode.
If pulled low, the i.MX233 will
attempt to boot from OTP.
GPIO
Debug: UART or SJTAG
USB-HOST
iMX233-OLinuXino-MICRO_rev_C
Olimex LTD. 2013, Plovdiv, Bulgaria
https://www.olimex.com

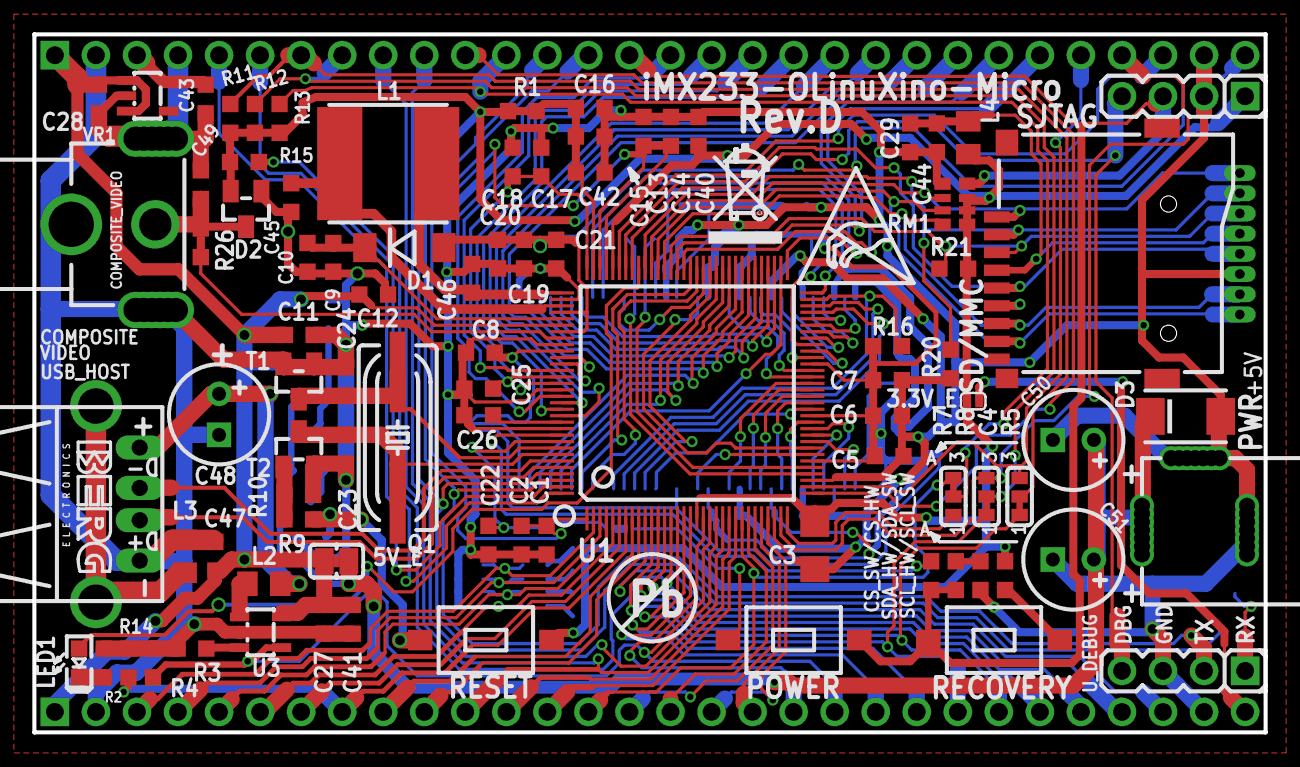
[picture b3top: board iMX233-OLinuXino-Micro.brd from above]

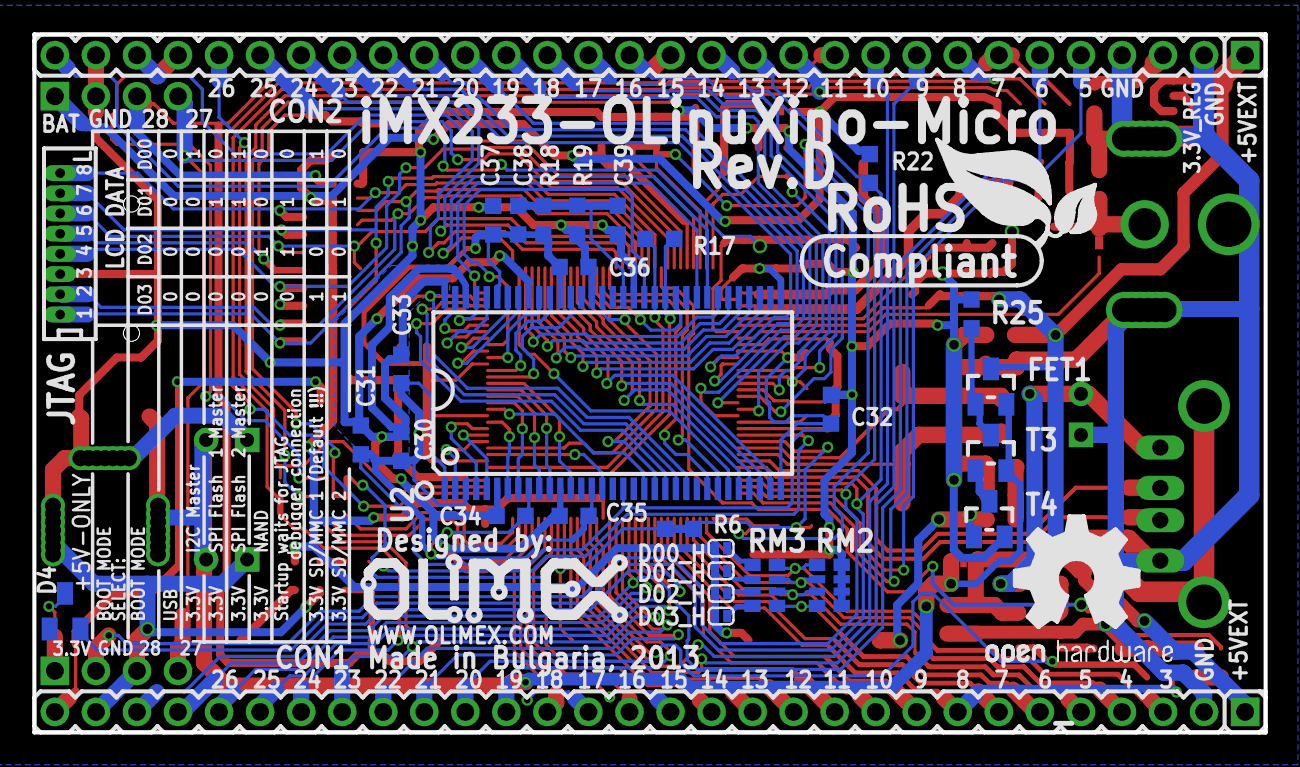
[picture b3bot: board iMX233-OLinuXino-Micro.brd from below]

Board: 4 copper layers, 76.2 x 43.2 mm, 124 parts (33 on the bottom side), 142 nets.

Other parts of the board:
SD/MMC: MICRO_SD/MMC_CP_NEWTFC-WPAPR-08; TFC-WPAPR-08
U$5: LOGO-OPENHARDWARE_8X8
U$8: OLIMEX1_V
U$9: PB
U$10: ESD_SYMBOL
U$11: RECYCLE_BIN1/8
U$12: ROHS

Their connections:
GND: SD/MMC.6; also elsewhere on the board
SD_VCC: SD/MMC.4; also elsewhere on the board
SSP1_CMD: SD/MMC.3; also elsewhere on the board
SSP1_DATA0: SD/MMC.7; also elsewhere on the board
SSP1_DATA1: SD/MMC.8; also elsewhere on the board
SSP1_DATA2: SD/MMC.1; also elsewhere on the board
SSP1_DATA3: SD/MMC.2; also elsewhere on the board
SSP1_SCK: SD/MMC.5; also elsewhere on the board
